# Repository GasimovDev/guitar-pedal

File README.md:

# Guitar effects pedal: overdrive, tremolo and delay on your own PCB

A digital guitar pedal. Guitar in, an STM32 microcontroller runs three effects
(overdrive, then tremolo, then delay), and the sound comes out to your amp.
It has six knobs, three footswitches and three LEDs.

```
guitar -> input buffer -> ADC (PCM1808) -> STM32F411 (DSP) -> DAC (PCM5102A) -> output stage -> amp
              op-amp          24-bit          C firmware          32-bit            op-amp
```

| Effect | Knobs | Footswitch / LED |
|---|---|---|
| Overdrive | DRIVE (gain 1x to 151x), TONE (800 Hz to 8 kHz) | OD, red LED |
| Tremolo | RATE (0.5 to 12 Hz), DEPTH (0 to 100 %) | TREM, yellow LED blinks at the rate |
| Delay | TIME (40 to 800 ms), REPEATS (0 to 90 % feedback) | DELAY, green LED |

**What you do next is in the [build guide](https://claude.ai/code/artifact/68aed441-7a6f-4b3e-b3b9-c396d0ad24f2).**
It covers only the jobs that need your hands: ordering, soldering, flashing,
measuring and drilling.

## Parts I picked, and why

| Choice | Why |
|---|---|
| **WeAct Black Pill, STM32F411CEU6** (plugs into sockets) | Cheap, very well documented, has a hardware floating-point unit and full-duplex I2S. On sockets, so you can unplug it to flash it and the factory never touches it. |
| **PCM1808 ADC + PCM5102A DAC** | The standard hobby I2S audio pair. Few support parts, cheap, and the DAC makes its own negative supply, so its output is centred on 0 V. |
| **OPA1678 op-amp, single 9 V supply** | Low noise, rail-to-rail output. Works from the pedal's 9 V with a 4.3 V "virtual ground" (VBIAS). |
| **9 V DC, centre-negative** | The normal guitar-pedal power supply. |
| **KiCad 7** | Free, and the factory accepts its files. |
| **Bare-metal C (CMSIS registers, no HAL)** | Small, and every line is readable. Builds with `arm-none-eabi-gcc` and `make`. |
| **JLCPCB assembly, bottom side only** | All 79 small surface-mount parts are soldered by the factory. You solder only big through-hole parts. |
| **Hammond 1590XX box (145 x 121 x 39 mm)** | Room for 6 knobs and 3 footswitches. |

## What is done, and how it was checked

| Part | Status | How it was checked |
|---|---|---|
| DSP effects (C) | Done | 9 automated tests on the PC, all pass: bypass is exact, overdrive THD goes from 0.6 % to 38 %, tremolo rate and depth, delay echo lands at 420.00 ms, maximum repeats die out, no clicks when switching. Run `make test` in `firmware/`. |
| Firmware for the STM32 | Done, builds | Compiles with no warnings: 8.8 KB flash, 81 KB RAM (most of it is the 0.83 s delay memory). **Not yet run on a real chip.** |
| Analog circuits | Done | ngspice simulation: input stage gain x1.45 with -3 dB points at 2.2 Hz and 59.6 kHz; output stage x0.308 with -3 dB at 1 Hz and 150 kHz. A hard strum (1 V peak) uses about 2.9 V of the ADC's 3 V range. See `sim/analog_sim.png` (also in `docs/img/`). |
| Schematic | Done | 9 sheets, 66 nets. A script checks every pin against the design list: 271 pins, 0 errors. |
| PCB | Done | 85 x 76 mm, 2 layers, ground pour on both sides. KiCad design-rule check: **0 errors, 0 unconnected**. 3 warnings remain: three through-hole ground pads have 1 thermal spoke instead of 2 (still connected; harmless). |
| Factory files | Done | Gerbers + drill, BOM and pick-and-place for JLCPCB, a list of the parts you buy yourself. |
| Enclosure | Done | 1:1 printable drilling template, hole positions taken from the PCB. |

### Things I could not check from here

1. **Nothing has been built or powered yet.** The firmware has not run on hardware, and the board has not been made.
2. **LCSC part numbers are blank in the BOM.** I can't reach the JLCPCB parts catalogue from here, so you pick each part in their BOM tool. The guide shows how.
3. **Black Pill pin order.** I took it from the stm32-base.org pin tables. Check it against your module before you order (the guide's first step).
4. **Box size.** The template is drawn for a 1590XX. Measure your own box.

## Files

```
guitar-pedal/
  README.md                     this file
  docs/design-notes.md          how every stage works, with the numbers
  docs/img/                     simulation plot, effect plots, PCB pictures
  firmware/
    build/pedal.bin, pedal.hex  ready to flash
    src/                        main.c, audio_io.c (I2S + DMA), controls.c (knobs, switches, LEDs), clock.c, uart.c, startup.c, board.h (pin map)
    dsp/effects.c               the three effects (plain C, also runs on a PC)
    host/                       PC test bench: `make test` runs the tests and writes demo WAVs to host/out/
    Makefile                    make / make flash-dfu / make flash-stlink / make test
  hardware/
    pedal.kicad_pro             open this in KiCad 7
    fab/pedal-gerbers.zip       upload to JLCPCB
    fab/bom_jlc.csv, cpl_jlc.csv   factory assembly files
    fab/hand_parts.csv          what you buy and solder yourself
    fab/schematic.pdf           the schematic, 9 pages
    fab/enclosure-drill-template.pdf   print at 100 %
    fab/pcb_top.png, pcb_bottom.png
    gen/                        Python scripts that generate the whole KiCad project
  sim/analog.cir, run_sim.py    ngspice simulation of the analog stages
```

### Rebuilding from the scripts (optional)

Everything in `hardware/` is generated by the scripts in `hardware/gen/`, run in
this order: `gen_libs.py`, `gen_sch.py`, `check_netlist.py`, `gen_pcb.py`,
`gen_pro.py`, `route.py`, `drc.py`, `export.py`, `enclosure.py`. They need KiCad 7's
Python module, and `route.py` also needs Java and `freerouting.jar` (Freerouting 2.5,
not included because it is 65 MB).

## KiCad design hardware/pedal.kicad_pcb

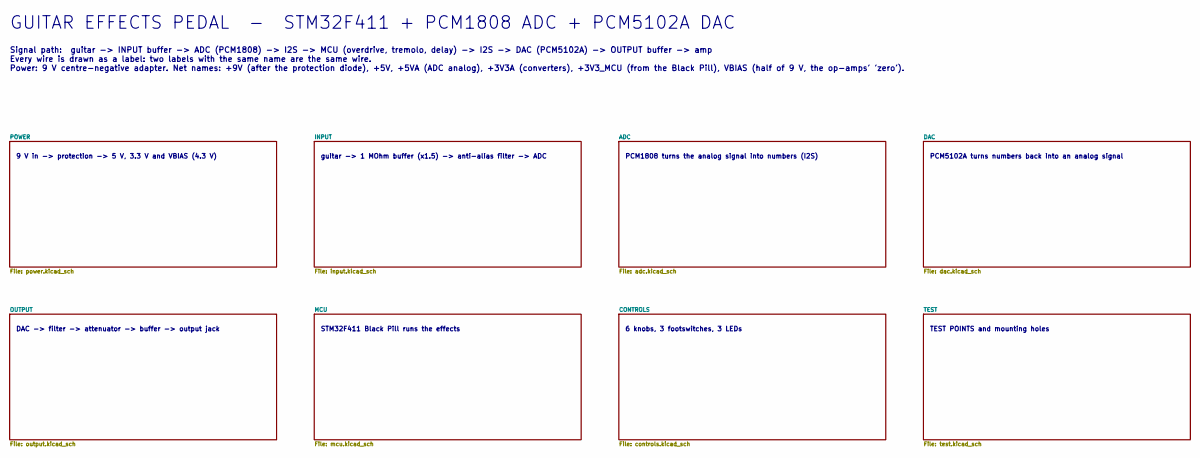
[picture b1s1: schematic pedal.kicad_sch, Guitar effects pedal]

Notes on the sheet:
GUITAR EFFECTS PEDAL - STM32F411 + PCM1808 ADC + PCM5102A DAC
Signal path: guitar -> INPUT buffer -> ADC (PCM1808) -> I2S -> MCU (overdrive, tremolo, delay) -> I2S -> DAC (PCM5102A) -> OUTPUT buffer -> amp Every wire is drawn as a label: two labels with the same name are the same wire. Power: 9 V centre-negative adapter. Net names: +9V (after the protection d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
9 V in -> protection -> 5 V, 3.3 V and VBIAS (4.3 V)
guitar -> 1 MOhm buffer (x1.5) -> anti-alias filter -> ADC
PCM1808 turns the analog signal into numbers (I2S)
PCM5102A turns numbers back into an analog signal
DAC -> filter -> attenuator -> buffer -> output jack
STM32F411 Black Pill runs the effects
6 knobs, 3 footswitches, 3 LEDs
TEST POINTS and mounting holes

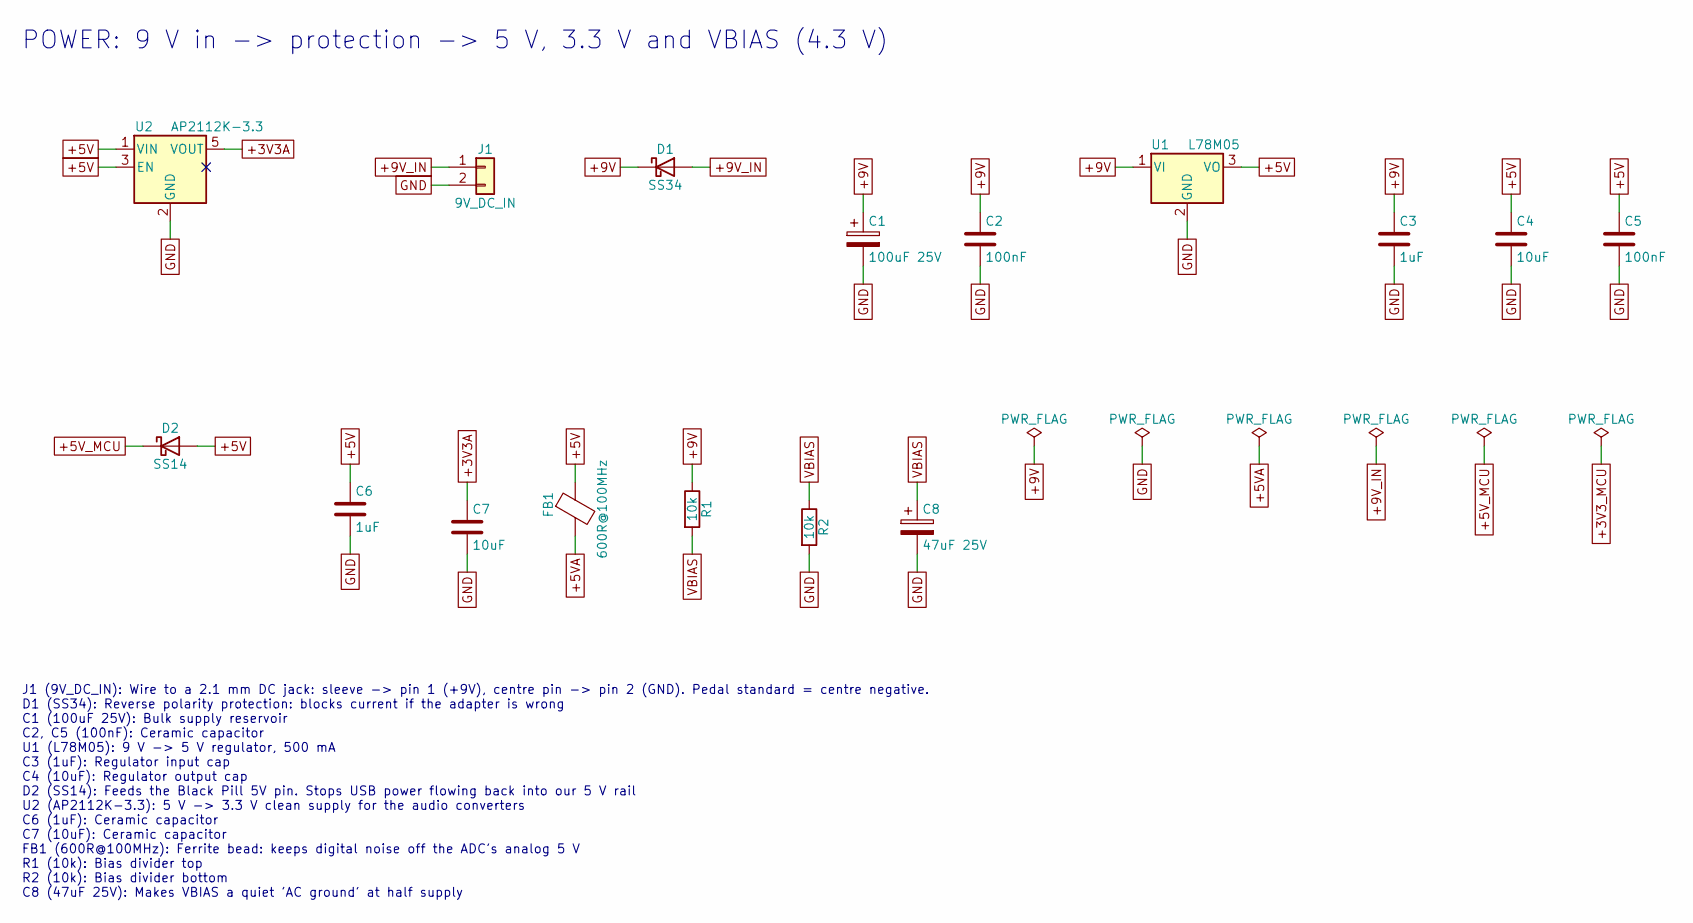
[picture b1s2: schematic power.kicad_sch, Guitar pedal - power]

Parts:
C1: 100uF 25V; CP_Elec_6.3x7.7; MPN 100uF 25V SMD electrolytic 6.3x7.7
C2, C5: 100nF; C_0805_2012Metric; MPN 0805 100nF X7R
C3, C6: 1uF; C_0805_2012Metric; MPN 0805 1uF X7R
C4, C7: 10uF; C_0805_2012Metric; MPN 0805 10uF X7R
C8: 47uF 25V; CP_Elec_6.3x5.4; MPN 47uF 25V SMD electrolytic 6.3x5.4
D1: SS34; D_SMA; MPN SS34
D2: SS14; D_SMA; MPN SS14
FB1: 600R@100MHz; L_0805_2012Metric; MPN BLM21PG601SN1D
J1: 9V_DC_IN; PinHeader_1x02_P2.54mm_Vertical; MPN 2.54mm header 1x2
R1, R2: 10k; R_0805_2012Metric; MPN 0805 10k 1%
U1: L78M05; TO-252-2; MPN L78M05CDT-TR
U2: AP2112K-3.3; SOT-23-5; MPN AP2112K-3.3TRG1

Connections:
+3V3A: C7.1, U2.5 (VOUT); also elsewhere on the board
+5V: C4.1, C5.1, C6.1, D2.2 (A), FB1.1, U1.3 (VO), U2.1 (VIN), U2.3 (EN); also elsewhere on the board
+5VA: FB1.2; also elsewhere on the board
+5V_MCU: D2.1 (K); also elsewhere on the board
+9V: C1.1, C2.1, C3.1, D1.1 (K), R1.1, U1.1 (VI); also elsewhere on the board
+9V_IN: D1.2 (A), J1.1
GND: C1.2, C2.2, C3.2, C4.2, C5.2, C6.2, C7.2, C8.2, J1.2, R2.2, U1.2 (GND), U2.2 (GND); also elsewhere on the board
VBIAS: C8.1, R1.2, R2.1; also elsewhere on the board

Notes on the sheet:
POWER: 9 V in -> protection -> 5 V, 3.3 V and VBIAS (4.3 V)
J1 (9V_DC_IN): Wire to a 2.1 mm DC jack: sleeve -> pin 1 (+9V), centre pin -> pin 2 (GND). Pedal standard = centre negative. D1 (SS34): Reverse polarity protection: blocks current if the adapter is wrong C1 (100uF 25V): Bulk supply reservoir C2, C5 (100nF): Ceramic capacitor U1 (L78M05): 9 V -> 5 V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

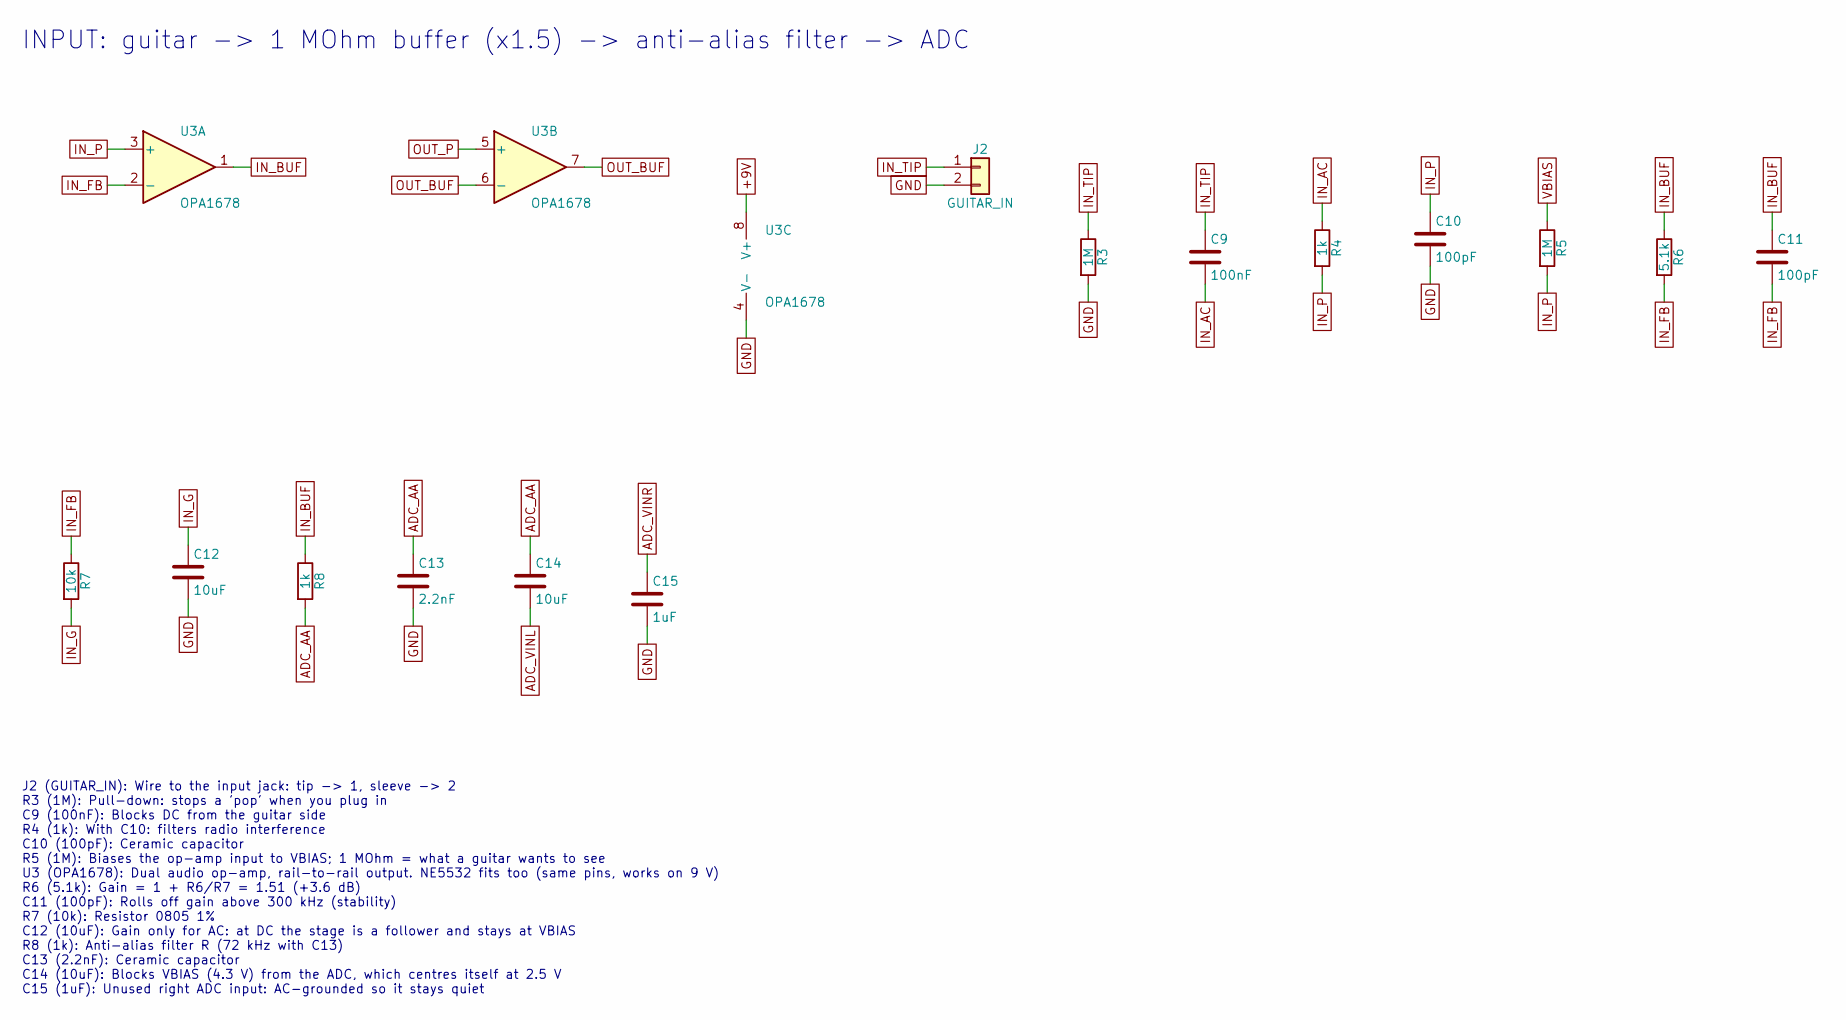
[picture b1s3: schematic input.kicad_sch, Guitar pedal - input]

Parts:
C9: 100nF; C_0805_2012Metric; MPN 0805 100nF X7R
C10, C11: 100pF; C_0805_2012Metric; MPN 0805 100pF C0G
C12, C14: 10uF; C_0805_2012Metric; MPN 0805 10uF X7R
C13: 2.2nF; C_0805_2012Metric; MPN 0805 2.2nF C0G
C15: 1uF; C_0805_2012Metric; MPN 0805 1uF X7R
J2: GUITAR_IN; PinHeader_1x02_P2.54mm_Vertical; MPN 2.54mm header 1x2
R3, R5: 1M; R_0805_2012Metric; MPN 0805 1M 1%
R4, R8: 1k; R_0805_2012Metric; MPN 0805 1k 1%
R6: 5.1k; R_0805_2012Metric; MPN 0805 5.1k 1%
R7: 10k; R_0805_2012Metric; MPN 0805 10k 1%
U3: OPA1678; SOIC-8_3.9x4.9mm_P1.27mm; MPN OPA1678IDR

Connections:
+9V: U3.8 (V+); also elsewhere on the board
ADC_AA: C13.1, C14.1, R8.2
ADC_VINL: C14.2; also elsewhere on the board
ADC_VINR: C15.1; also elsewhere on the board
GND: C10.2, C12.2, C13.2, C15.2, J2.2, R3.2, U3.4 (V-); also elsewhere on the board
IN_AC: C9.2, R4.1
IN_BUF: C11.1, R6.1, R8.1, U3.1; also elsewhere on the board
IN_FB: C11.2, R6.2, R7.1, U3.2 (-)
IN_G: C12.1, R7.2
IN_P: C10.1, R4.2, R5.2, U3.3 (+)
IN_TIP: C9.1, J2.1, R3.1
OUT_BUF: U3.6 (-), U3.7; also elsewhere on the board
OUT_P: U3.5 (+); also elsewhere on the board
VBIAS: R5.1; also elsewhere on the board

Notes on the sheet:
INPUT: guitar -> 1 MOhm buffer (x1.5) -> anti-alias filter -> ADC
J2 (GUITAR_IN): Wire to the input jack: tip -> 1, sleeve -> 2 R3 (1M): Pull-down: stops a 'pop' when you plug in C9 (100nF): Blocks DC from the guitar side R4 (1k): With C10: filters radio interference C10 (100pF): Ceramic capacitor R5 (1M): Biases the op-amp input to VBIAS; 1 MOhm = what a guitar 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

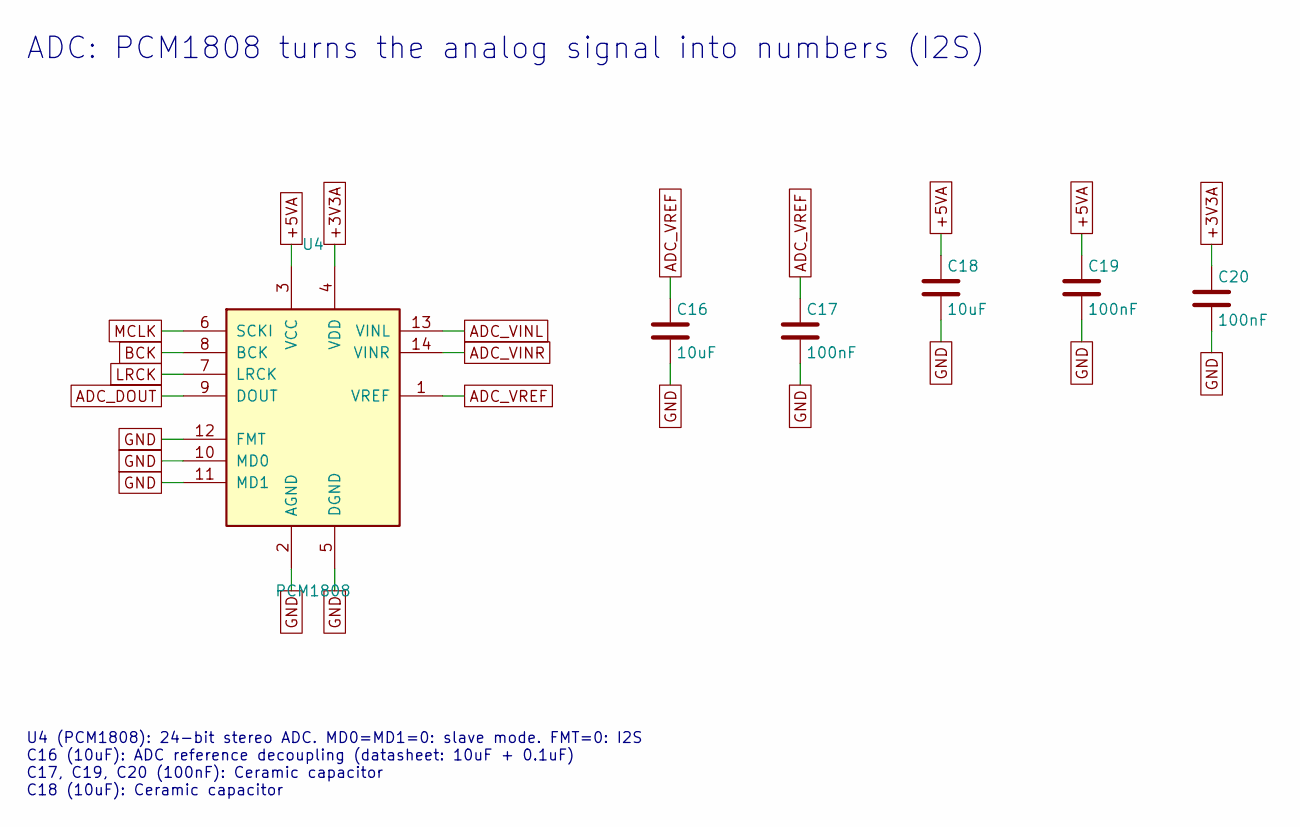
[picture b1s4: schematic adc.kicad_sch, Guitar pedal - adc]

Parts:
C16, C18: 10uF; C_0805_2012Metric; MPN 0805 10uF X7R
C17, C19, C20: 100nF; C_0805_2012Metric; MPN 0805 100nF X7R
U4: PCM1808; TSSOP-14_4.4x5mm_P0.65mm; MPN PCM1808PWR

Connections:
+3V3A: C20.1, U4.4 (VDD); also elsewhere on the board
+5VA: C18.1, C19.1, U4.3 (VCC); also elsewhere on the board
ADC_DOUT: U4.9 (DOUT); also elsewhere on the board
ADC_VINL: U4.13 (VINL); also elsewhere on the board
ADC_VINR: U4.14 (VINR); also elsewhere on the board
ADC_VREF: C16.1, C17.1, U4.1 (VREF)
BCK: U4.8 (BCK); also elsewhere on the board
GND: C16.2, C17.2, C18.2, C19.2, C20.2, U4.2 (AGND), U4.5 (DGND), U4.10 (MD0), U4.11 (MD1), U4.12 (FMT); also elsewhere on the board
LRCK: U4.7 (LRCK); also elsewhere on the board
MCLK: U4.6 (SCKI); also elsewhere on the board

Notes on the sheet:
ADC: PCM1808 turns the analog signal into numbers (I2S)
U4 (PCM1808): 24-bit stereo ADC. MD0=MD1=0: slave mode. FMT=0: I2S C16 (10uF): ADC reference decoupling (datasheet: 10uF + 0.1uF) C17, C19, C20 (100nF): Ceramic capacitor C18 (10uF): Ceramic capacitor

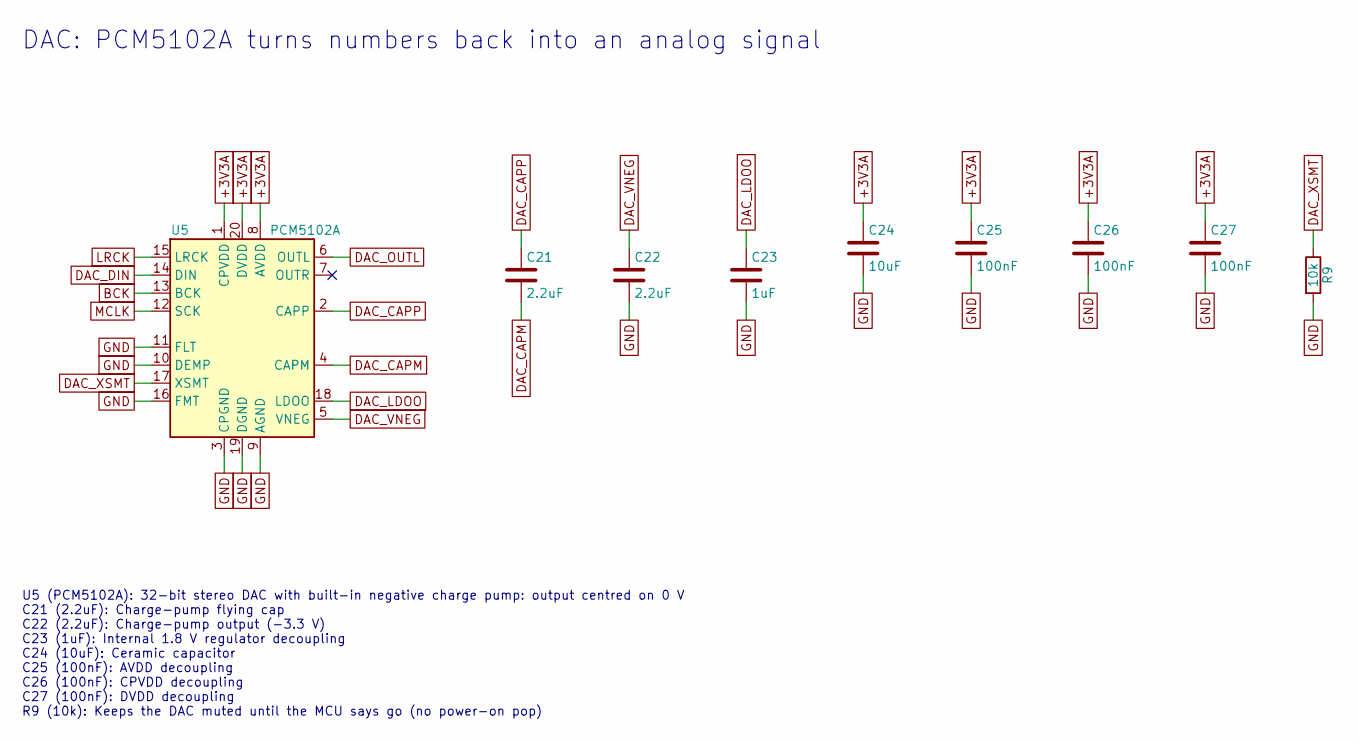
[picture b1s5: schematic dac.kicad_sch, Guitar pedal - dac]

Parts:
C21, C22: 2.2uF; C_0805_2012Metric; MPN 0805 2.2uF X7R
C23: 1uF; C_0805_2012Metric; MPN 0805 1uF X7R
C24: 10uF; C_0805_2012Metric; MPN 0805 10uF X7R
C25, C26, C27: 100nF; C_0805_2012Metric; MPN 0805 100nF X7R
R9: 10k; R_0805_2012Metric; MPN 0805 10k 1%
U5: PCM5102A; TSSOP-20_4.4x6.5mm_P0.65mm; MPN PCM5102APWR

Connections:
+3V3A: C24.1, C25.1, C26.1, C27.1, U5.1 (CPVDD), U5.8 (AVDD), U5.20 (DVDD); also elsewhere on the board
BCK: U5.13 (BCK); also elsewhere on the board
DAC_CAPM: C21.2, U5.4 (CAPM)
DAC_CAPP: C21.1, U5.2 (CAPP)
DAC_DIN: U5.14 (DIN); also elsewhere on the board
DAC_LDOO: C23.1, U5.18 (LDOO)
DAC_OUTL: U5.6 (OUTL); also elsewhere on the board
DAC_VNEG: C22.1, U5.5 (VNEG)
DAC_XSMT: R9.1, U5.17 (XSMT); also elsewhere on the board
GND: C22.2, C23.2, C24.2, C25.2, C26.2, C27.2, R9.2, U5.3 (CPGND), U5.9 (AGND), U5.10 (DEMP), U5.11 (FLT), U5.16 (FMT), U5.19 (DGND); also elsewhere on the board
LRCK: U5.15 (LRCK); also elsewhere on the board
MCLK: U5.12 (SCK); also elsewhere on the board

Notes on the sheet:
DAC: PCM5102A turns numbers back into an analog signal
U5 (PCM5102A): 32-bit stereo DAC with built-in negative charge pump: output centred on 0 V C21 (2.2uF): Charge-pump flying cap C22 (2.2uF): Charge-pump output (-3.3 V) C23 (1uF): Internal 1.8 V regulator decoupling C24 (10uF): Ceramic capacitor C25 (100nF): AVDD decoupling C26 (100nF): CPVDD decoup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

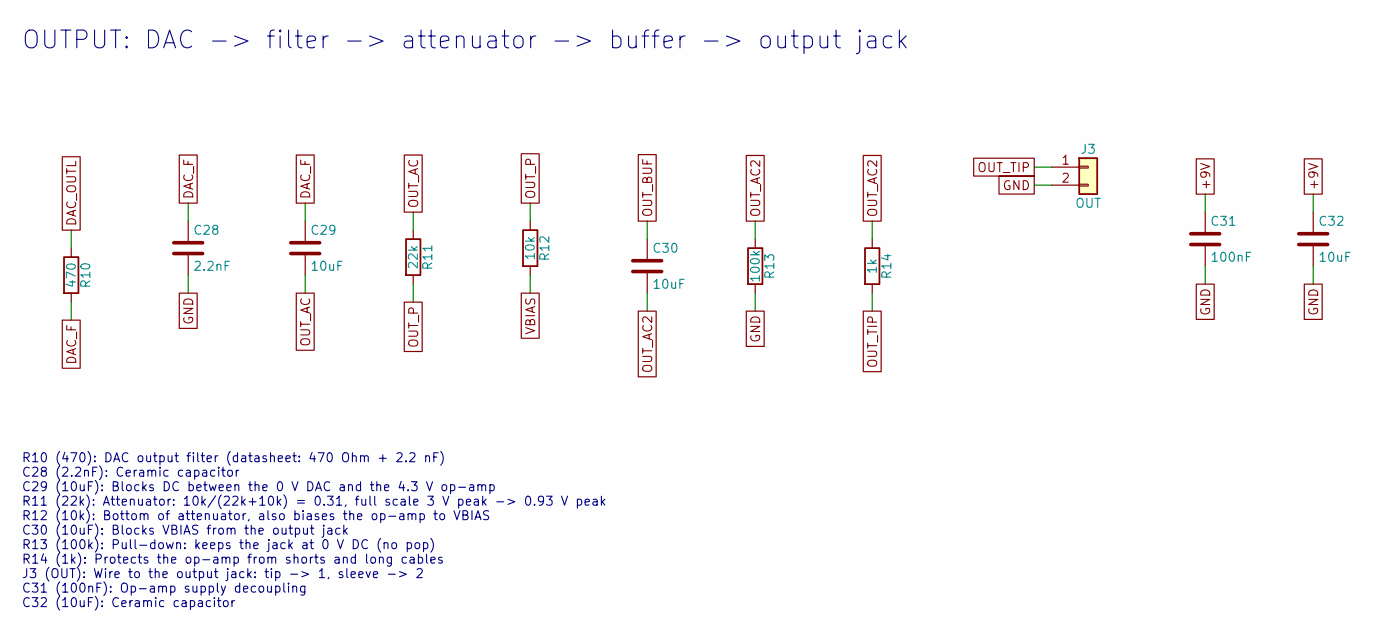
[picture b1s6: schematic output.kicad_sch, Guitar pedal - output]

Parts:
C28: 2.2nF; C_0805_2012Metric; MPN 0805 2.2nF C0G
C29, C30, C32: 10uF; C_0805_2012Metric; MPN 0805 10uF X7R
C31: 100nF; C_0805_2012Metric; MPN 0805 100nF X7R
J3: OUT; PinHeader_1x02_P2.54mm_Vertical; MPN 2.54mm header 1x2
R10: 470; R_0805_2012Metric; MPN 0805 470 1%
R11: 22k; R_0805_2012Metric; MPN 0805 22k 1%
R12: 10k; R_0805_2012Metric; MPN 0805 10k 1%
R13: 100k; R_0805_2012Metric; MPN 0805 100k 1%
R14: 1k; R_0805_2012Metric; MPN 0805 1k 1%

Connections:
+9V: C31.1, C32.1; also elsewhere on the board
DAC_F: C28.1, C29.1, R10.2
DAC_OUTL: R10.1; also elsewhere on the board
GND: C28.2, C31.2, C32.2, J3.2, R13.2; also elsewhere on the board
OUT_AC: C29.2, R11.1
OUT_AC2: C30.2, R13.1, R14.1
OUT_BUF: C30.1; also elsewhere on the board
OUT_P: R11.2, R12.1; also elsewhere on the board
OUT_TIP: J3.1, R14.2
VBIAS: R12.2; also elsewhere on the board

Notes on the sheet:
OUTPUT: DAC -> filter -> attenuator -> buffer -> output jack
R10 (470): DAC output filter (datasheet: 470 Ohm + 2.2 nF) C28 (2.2nF): Ceramic capacitor C29 (10uF): Blocks DC between the 0 V DAC and the 4.3 V op-amp R11 (22k): Attenuator: 10k/(22k+10k) = 0.31, full scale 3 V peak -> 0.93 V peak R12 (10k): Bottom of attenuator, also biases the op-amp to VBIAS C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

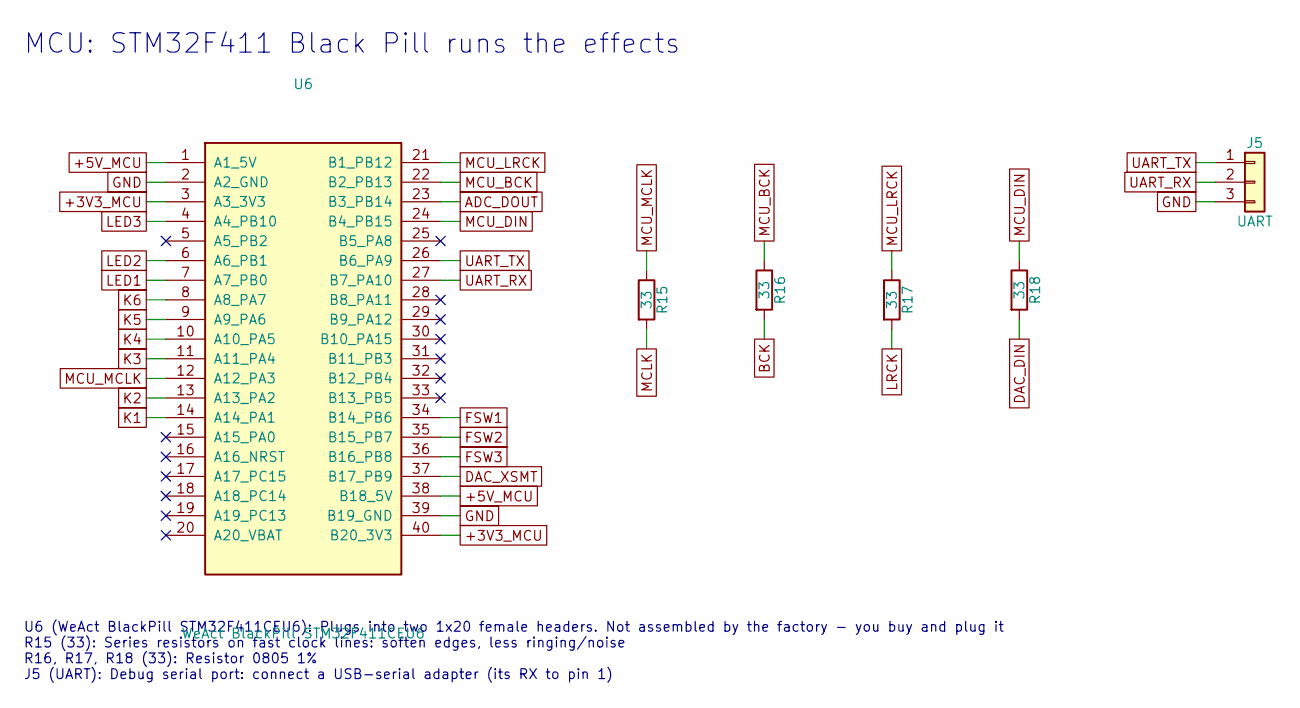
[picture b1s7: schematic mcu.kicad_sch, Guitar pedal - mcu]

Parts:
J5: UART; PinHeader_1x03_P2.54mm_Vertical; MPN 2.54mm header 1x3
R15, R16, R17, R18: 33; R_0805_2012Metric; MPN 0805 33 1%
U6: WeAct BlackPill STM32F411CEU6; BlackPill_Sockets; MPN WeAct BlackPill V3.0 STM32F411CEU6 (25 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

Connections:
+3V3_MCU: U6.3 (A3_3V3), U6.40 (B20_3V3); also elsewhere on the board
+5V_MCU: U6.1 (A1_5V), U6.38 (B18_5V); also elsewhere on the board
ADC_DOUT: U6.23 (B3_PB14); also elsewhere on the board
BCK: R16.2; also elsewhere on the board
DAC_DIN: R18.2; also elsewhere on the board
DAC_XSMT: U6.37 (B17_PB9); also elsewhere on the board
FSW1: U6.34 (B14_PB6); also elsewhere on the board
FSW2: U6.35 (B15_PB7); also elsewhere on the board
FSW3: U6.36 (B16_PB8); also elsewhere on the board
GND: J5.3, U6.2 (A2_GND), U6.39 (B19_GND); also elsewhere on the board
K1: U6.14 (A14_PA1); also elsewhere on the board
K2: U6.13 (A13_PA2); also elsewhere on the board
K3: U6.11 (A11_PA4); also elsewhere on the board
K4: U6.10 (A10_PA5); also elsewhere on the board
K5: U6.9 (A9_PA6); also elsewhere on the board
K6: U6.8 (A8_PA7); also elsewhere on the board
LED1: U6.7 (A7_PB0); also elsewhere on the board
LED2: U6.6 (A6_PB1); also elsewhere on the board
LED3: U6.4 (A4_PB10); also elsewhere on the board
LRCK: R17.2; also elsewhere on the board
MCLK: R15.2; also elsewhere on the board
MCU_BCK: R16.1, U6.22 (B2_PB13)
MCU_DIN: R18.1, U6.24 (B4_PB15)
MCU_LRCK: R17.1, U6.21 (B1_PB12)
MCU_MCLK: R15.1, U6.12 (A12_PA3)
UART_RX: J5.2, U6.27 (B7_PA10)
UART_TX: J5.1, U6.26 (B6_PA9)

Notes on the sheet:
MCU: STM32F411 Black Pill runs the effects
U6 (WeAct BlackPill STM32F411CEU6): Plugs into two 1x20 female headers. Not assembled by the factory - you buy and plug it R15 (33): Series resistors on fast clock lines: soften edges, less ringing/noise R16, R17, R18 (33): Resistor 0805 1% J5 (UART): Debug serial port: connect a USB-serial adapter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

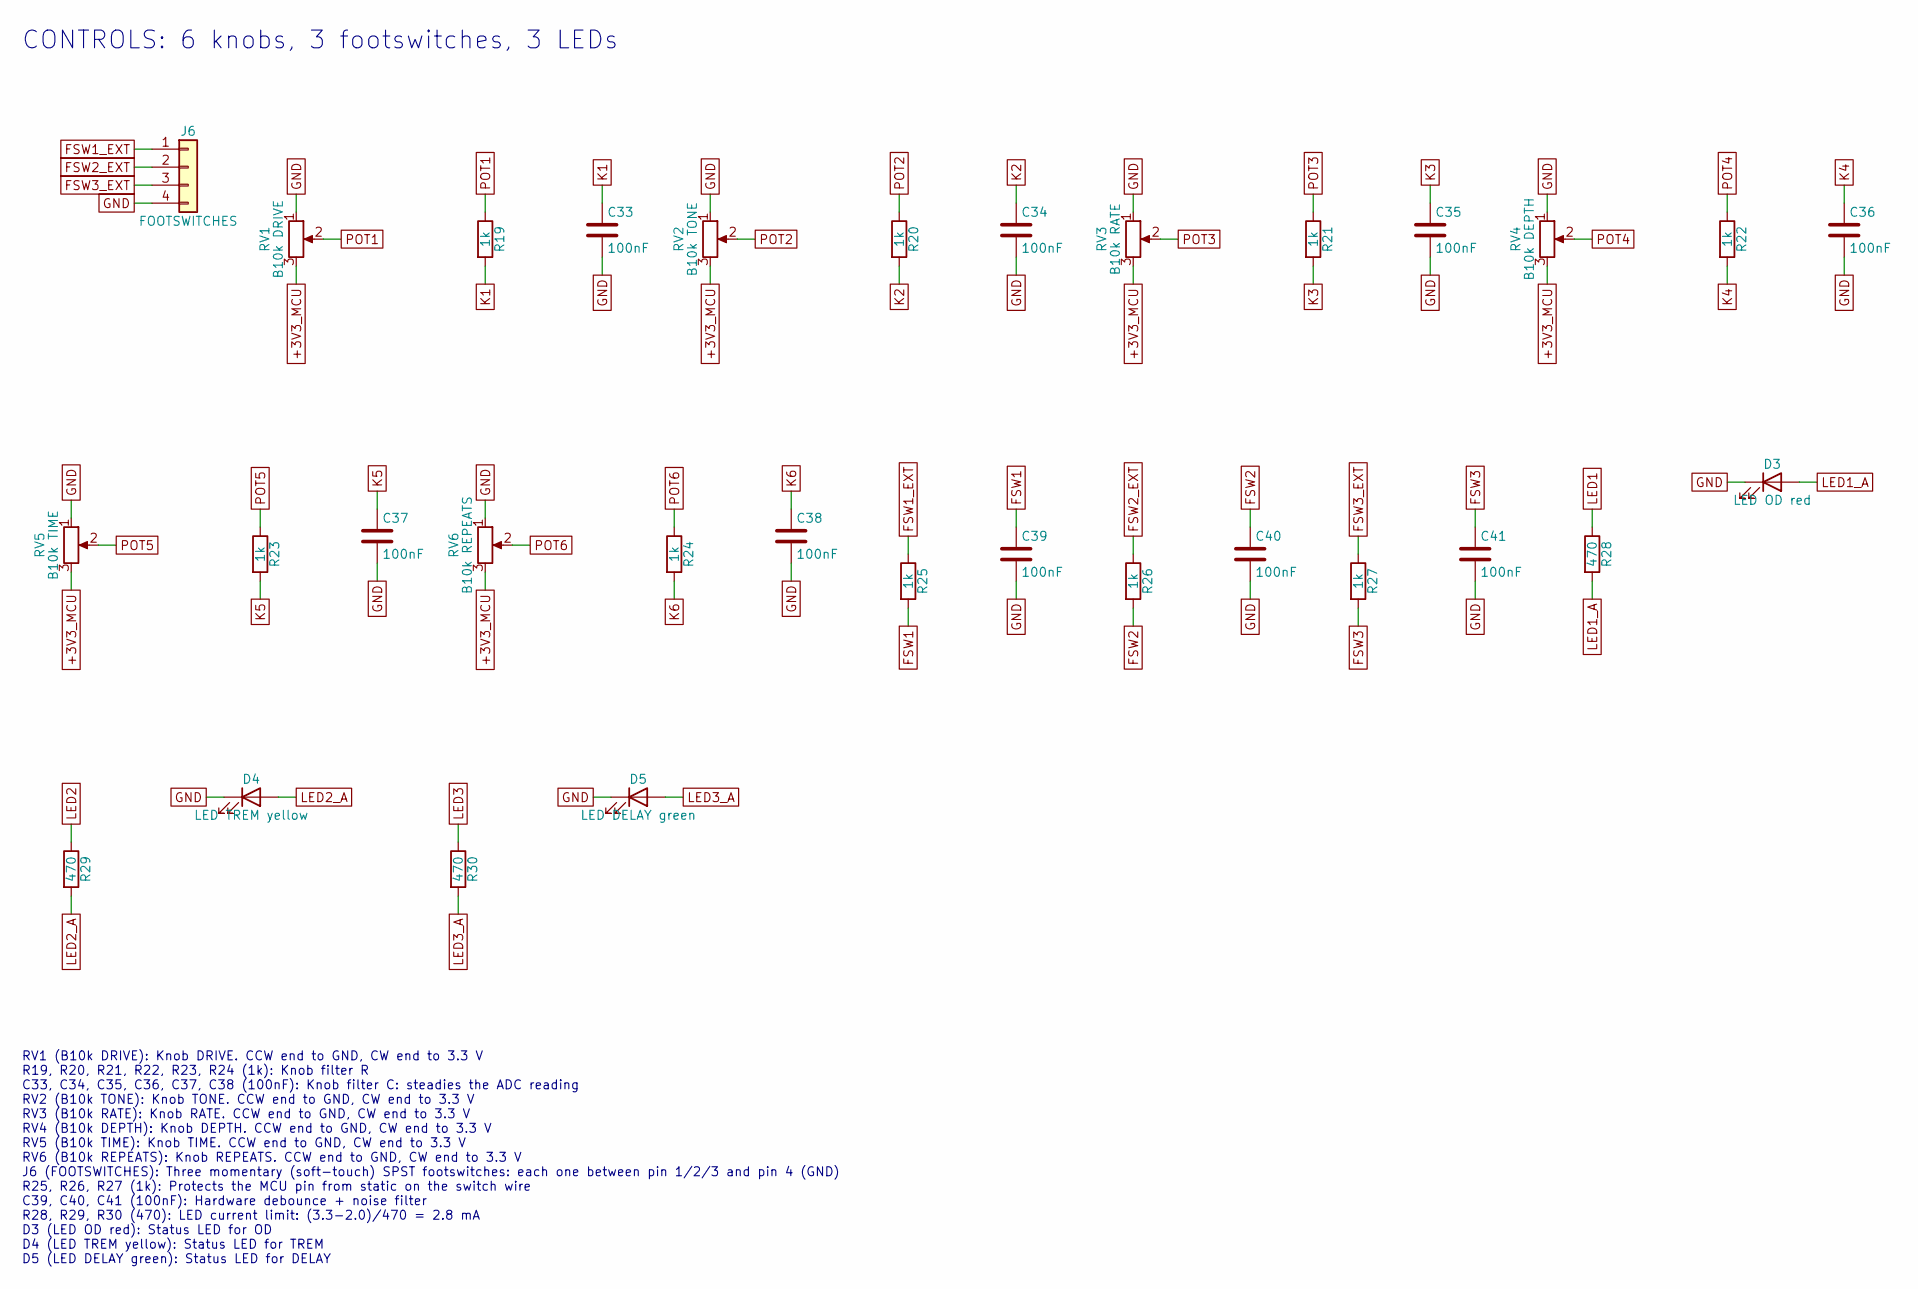
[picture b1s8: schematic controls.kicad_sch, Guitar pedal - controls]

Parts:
C33, C34, C35, C36, C37, C38, C39, C40, C41: 100nF; C_0805_2012Metric; MPN 0805 100nF X7R
D3: LED OD red; LED_D3.0mm; MPN 3mm red LED, diffused
D4: LED TREM yellow; LED_D3.0mm; MPN 3mm yellow LED, diffused
D5: LED DELAY green; LED_D3.0mm; MPN 3mm green LED, diffused
J6: FOOTSWITCHES; PinHeader_1x04_P2.54mm_Vertical; MPN 2.54mm header 1x4
R19, R20, R21, R22, R23, R24, R25, R26, R27: 1k; R_0805_2012Metric; MPN 0805 1k 1%
R28, R29, R30: 470; R_0805_2012Metric; MPN 0805 470 1%
RV1: B10k DRIVE; Potentiometer_Alpha_RD901F-40-00D_Single_Vertical; MPN Alpha RD901F-40 9mm B10K linear
RV2: B10k TONE; Potentiometer_Alpha_RD901F-40-00D_Single_Vertical; MPN Alpha RD901F-40 9mm B10K linear
RV3: B10k RATE; Potentiometer_Alpha_RD901F-40-00D_Single_Vertical; MPN Alpha RD901F-40 9mm B10K linear
RV4: B10k DEPTH; Potentiometer_Alpha_RD901F-40-00D_Single_Vertical; MPN Alpha RD901F-40 9mm B10K linear
RV5: B10k TIME; Potentiometer_Alpha_RD901F-40-00D_Single_Vertical; MPN Alpha RD901F-40 9mm B10K linear
RV6: B10k REPEATS; Potentiometer_Alpha_RD901F-40-00D_Single_Vertical; MPN Alpha RD901F-40 9mm B10K linear

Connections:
+3V3_MCU: RV1.3, RV2.3, RV3.3, RV4.3, RV5.3, RV6.3; also elsewhere on the board
FSW1: C39.1, R25.2; also elsewhere on the board
FSW1_EXT: J6.1, R25.1
FSW2: C40.1, R26.2; also elsewhere on the board
FSW2_EXT: J6.2, R26.1
FSW3: C41.1, R27.2; also elsewhere on the board
FSW3_EXT: J6.3, R27.1
GND: C33.2, C34.2, C35.2, C36.2, C37.2, C38.2, C39.2, C40.2, C41.2, D3.1 (K), D4.1 (K), D5.1 (K), J6.4, RV1.1, RV2.1, RV3.1, RV4.1, RV5.1, RV6.1; also elsewhere on the board
K1: C33.1, R19.2; also elsewhere on the board
K2: C34.1, R20.2; also elsewhere on the board
K3: C35.1, R21.2; also elsewhere on the board
K4: C36.1, R22.2; also elsewhere on the board
K5: C37.1, R23.2; also elsewhere on the board
K6: C38.1, R24.2; also elsewhere on the board
LED1: R28.1; also elsewhere on the board
LED1_A: D3.2 (A), R28.2
LED2: R29.1; also elsewhere on the board
LED2_A: D4.2 (A), R29.2
LED3: R30.1; also elsewhere on the board
LED3_A: D5.2 (A), R30.2
POT1: R19.1, RV1.2
POT2: R20.1, RV2.2
POT3: R21.1, RV3.2
POT4: R22.1, RV4.2
POT5: R23.1, RV5.2
POT6: R24.1, RV6.2

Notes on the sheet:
CONTROLS: 6 knobs, 3 footswitches, 3 LEDs
RV1 (B10k DRIVE): Knob DRIVE. CCW end to GND, CW end to 3.3 V R19, R20, R21, R22, R23, R24 (1k): Knob filter R C33, C34, C35, C36, C37, C38 (100nF): Knob filter C: steadies the ADC reading RV2 (B10k TONE): Knob TONE. CCW end to GND, CW end to 3.3 V RV3 (B10k RATE): Knob RATE. CCW end to GND, CW end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

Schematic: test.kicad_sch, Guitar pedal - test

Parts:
TP1: +9V; TestPoint_THTPad_D2.0mm_Drill1.0mm; MPN (no part - bare pad, probe here)
TP2: +5V; TestPoint_THTPad_D2.0mm_Drill1.0mm; MPN (no part - bare pad, probe here)
TP3: +3V3A; TestPoint_THTPad_D2.0mm_Drill1.0mm; MPN (no part - bare pad, probe here)
TP4: VBIAS; TestPoint_THTPad_D2.0mm_Drill1.0mm; MPN (no part - bare pad, probe here)
TP5, TP6: GND; TestPoint_THTPad_D2.0mm_Drill1.0mm; MPN (no part - bare pad, probe here)
TP7: MCLK; TestPoint_THTPad_D2.0mm_Drill1.0mm; MPN (no part - bare pad, probe here)
TP8: BCK; TestPoint_THTPad_D2.0mm_Drill1.0mm; MPN (no part - bare pad, probe here)
TP9: LRCK; TestPoint_THTPad_D2.0mm_Drill1.0mm; MPN (no part - bare pad, probe here)
TP10: IN_BUF; TestPoint_THTPad_D2.0mm_Drill1.0mm; MPN (no part - bare pad, probe here)
TP11: DAC_OUTL; TestPoint_THTPad_D2.0mm_Drill1.0mm; MPN (no part - bare pad, probe here)
TP12: OUT_BUF; TestPoint_THTPad_D2.0mm_Drill1.0mm; MPN (no part - bare pad, probe here)

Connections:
+3V3A: TP3.1; also elsewhere on the board
+5V: TP2.1; also elsewhere on the board
+9V: TP1.1; also elsewhere on the board
BCK: TP8.1; also elsewhere on the board
DAC_OUTL: TP11.1; also elsewhere on the board
GND: TP5.1, TP6.1; also elsewhere on the board
IN_BUF: TP10.1; also elsewhere on the board
LRCK: TP9.1; also elsewhere on the board
MCLK: TP7.1; also elsewhere on the board
OUT_BUF: TP12.1; also elsewhere on the board
VBIAS: TP4.1; also elsewhere on the board

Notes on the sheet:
TEST POINTS and mounting holes
TP1 (+9V): Measure here with the multimeter or scope TP2 (+5V): Measure here with the multimeter or scope TP3 (+3V3A): Measure here with the multimeter or scope TP4 (VBIAS): Measure here with the multimeter or scope TP5, TP6 (GND): Measure here with the multimeter or scope TP7 (MCLK): Measure here 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
